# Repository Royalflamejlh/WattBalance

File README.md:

# ECE445-Wattbalance

## Introduction
Our senior design project focused on the development of a Kibble balance, also known as a watt balance. This is an instrument capable of precise measurements based on electromagnetic forces and the definition of a kilogram based on fundamental constants. Our design is focused on the two main working modes of a watt balance, velocity mode in which a coil constant is calculated, and force mode in which that coil constant is used to realize some mass. We designed a custom 3D printed balance, along with a custom PCB to drive the measurements. Once assembled we found that velocity mode on our balance was inaccurate, but our force mode performed as expected. With a manual estimation of the coil constant, we were able to get accurate mass readings from our balance. The designs, failures, and successes are all documented in the following report.

## Features
- **Custom 3D Printed Balance**: Designed for precise measurements.
- **Custom PCB**: For accurate measurement and control.
- **Velocity Mode**: Calculates the coil constant.
- **Force Mode**: Uses the coil constant to measure mass accurately.
- **Manual Estimation**: Allows for accurate mass readings.

## Read More
For more detailed information view:
- [Proposal](Documentation/proposal2.pdf)
- [Design Document](Documentation/design_document1.pdf)
- [Final Presentation](Documentation/other1.pdf)
- [Final Report](Documentation/final.pdf)

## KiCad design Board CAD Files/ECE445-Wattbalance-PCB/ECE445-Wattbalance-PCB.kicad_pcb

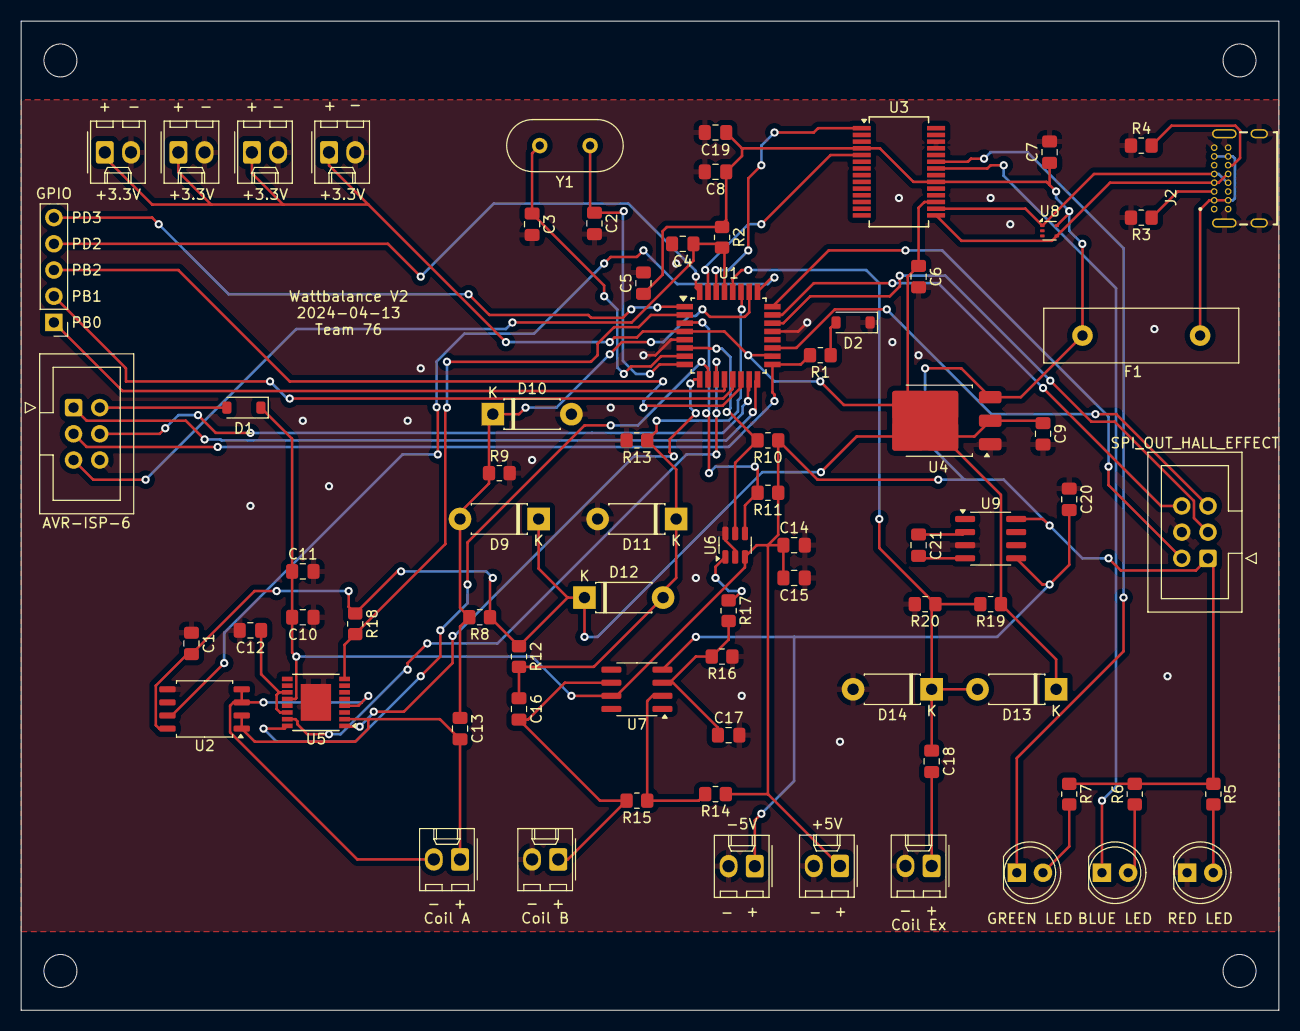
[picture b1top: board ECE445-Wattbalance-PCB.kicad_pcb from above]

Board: 2 copper layers, 121.9 x 95.9 mm, 80 parts (0 on the bottom side), 53 nets.

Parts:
C1: 0.1 µF; C_0805_2012Metric_Pad1.18x1.45mm_HandSolder
C2, C3: 22p; C_0805_2012Metric_Pad1.18x1.45mm_HandSolder
C4, C5: 100n; C_0805_2012Metric_Pad1.18x1.45mm_HandSolder
C6, C7, C8, C13, C16, C18: .1uF; C_0805_2012Metric_Pad1.18x1.45mm_HandSolder
C9, C11, C14, C19, C20, C21: 10uF; C_0805_2012Metric_Pad1.18x1.45mm_HandSolder
C10, C15: .1uf; C_0805_2012Metric_Pad1.18x1.45mm_HandSolder
C12: 2.2uF; C_0805_2012Metric_Pad1.18x1.45mm_HandSolder
C17: 0.1uF; C_0805_2012Metric_Pad1.18x1.45mm_HandSolder
D1: MBR0520; D_SOD-123
D2: D; D_SOD-123
D3: GREEN LED; LED_D5.0mm
D4: BLUE LED; LED_D5.0mm
D5: RED LED; LED_D5.0mm
D9, D10, D11, D12, D13, D14: 1N5819; D_DO-41_SOD81_P7.62mm_Horizontal
F1: 1A; Fuse_Littelfuse-LVR100
H1, H2, H3, H4: MountingHole; MountingHole_3.2mm_M3
J1: AVR-ISP-6; IDC-Header_2x03_P2.54mm_Vertical
J2: USB4085-GF-A_REVB; GCT_USB4085-GF-A_REVB
J3: SPI_OUT_HALL_EFFECT; IDC-Header_2x03_P2.54mm_Vertical
J4: GPIO; PinHeader_1x05_P2.54mm_Vertical
J5: Coil A; Molex_KK-254_AE-6410-02A_1x02_P2.54mm_Vertical
J6: Coil B; Molex_KK-254_AE-6410-02A_1x02_P2.54mm_Vertical
J7: Coil Ex; Molex_KK-254_AE-6410-02A_1x02_P2.54mm_Vertical
J8: -5V; Molex_KK-254_AE-6410-02A_1x02_P2.54mm_Vertical
J9, J11, J12, J13: +3.3V; Molex_KK-254_AE-6410-02A_1x02_P2.54mm_Vertical
J10: +5V; Molex_KK-254_AE-6410-02A_1x02_P2.54mm_Vertical
R1: 330R; R_0805_2012Metric_Pad1.20x1.40mm_HandSolder
R2, R8, R9, R10, R11, R12, R13, R18, R19, R20: 10k; R_0805_2012Metric_Pad1.20x1.40mm_HandSolder
R3, R4: 5.1k; R_0805_2012Metric_Pad1.20x1.40mm_HandSolder
R5, R6, R7: 470R; R_0805_2012Metric_Pad1.20x1.40mm_HandSolder
R14: 16k; R_0805_2012Metric_Pad1.20x1.40mm_HandSolder
R15, R16: 4k; R_0805_2012Metric_Pad1.20x1.40mm_HandSolder
R17: 6k; R_0805_2012Metric_Pad1.20x1.40mm_HandSolder
U1: ATmega328PB-A; TQFP-32_7x7mm_P0.8mm
U2: ACS70331EOLCTR-2P5B3; SOIC-8_5.23x5.23mm_P1.27mm
U3: FT232RL; SSOP-28_5.3x10.2mm_P0.65mm
U4: LM1117DT-3.3; TO-252-3_TabPin2
U5: DRV8848; TSSOP-16-1EP_4.4x5mm_P0.65mm
U6: MCP4725A2T-E/CH; SOT-23-6
U7: OPA188AIDBVR; SOIC-8_3.9x4.9mm_P1.27mm
U8: TPD3E001DRLR; SOT-553
U9: ICL7660; SOIC-8_3.9x4.9mm_P1.27mm
Y1: 16MHz; Crystal_HC49-U_Vertical

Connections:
+3.3V: C1.2, C6.1, C9.1, D9.1 (K), D12.1 (K), D13.1 (K), J9.1, J11.1, J12.1, J13.1, R8.1, R12.1, R18.1, R19.1, U1.4 (VCC), U1.18 (AVCC), U2.8 (VCC), U3.17 (3V3OUT), U4.2 (VO)
+5V: C5.1, C7.1, C8.1, C10.2, C11.1, C14.1, C15.2, C19.1, D1.1 (K), F1.2, J3.1, J10.1, R2.1, R5.1, R6.2, R7.1, R10.1, R11.1, R14.1, U3.4 (VCCIO), U3.20 (VCC), U4.3 (VI), U5.12 (VM), U6.3 (VDD), U7.7 (V+), U8.5, U9.8 (V+)
-5V: C20.2, J8.1, U7.4 (V-), U9.5 (VOUT)
/ACS70331_Vout: U1.25 (PC2), U2.7 (VIOUT)
/CoilA+: C13.2, J5.1, U2.1 (IP+), U2.2 (IP+), U5.2 (AOUT1)
/CoilA-: J5.2, U2.3 (IP-), U2.4 (IP-), U5.4 (AOUT2)
/CoilA_ADC: C13.1, D9.2 (A), D10.1 (K), R8.2, R9.1, U1.26 (PC3)
/CoilB+: C16.2, J6.1, R15.2, U7.6
/CoilB_ADC: C16.1, D11.1 (K), D12.2 (A), R12.2, R13.1, U1.27 (PC4)
/EXT+: C18.2, J7.1
/EXT_ADC: C18.1, D13.2 (A), D14.1 (K), R19.2, R20.1, U1.28 (PC5)
/HE_MISO: J3.6, U1.23 (PC0)
/HE_SCK: J3.2, U1.24 (PC1)
/H_FAULT: R18.2, U1.2 (PD4), U5.8 (~FAULT)
/H_SLEEP: U1.9 (PD5), U5.1 (~SLEEP)
/MISO: J1.1 (MISO), U1.16 (PB4)
/MOSI: J1.4 (MOSI), U1.15 (PB3)
/OUTA: J4.1, U1.12 (PB0)
/OUTB: J4.2, U1.13 (PB1)
/OUTC: J4.3, U1.14 (PB2)
/OUTD: J4.4, U1.32 (PD2)
/OUTE: J4.5, U1.1 (PD3)
/PWMA: U1.10 (PD6), U5.16 (AIN1)
/PWMB: U1.11 (PD7), U5.15 (AIN2)
/RST: C4.1, J1.5 (~RST), R2.2, U1.29 (~RESET/PC6)
/RX: U1.31 (PD1), U3.5 (RXD)
/RXLED: D4.1 (K), U3.22 (CBUS1)
/SCK: J1.3 (SCK), R1.2, U1.17 (PB5)
/SCL: R10.2, U1.6 (PE1), U6.5 (SCL)
/SDA: R11.2, U1.3 (PE0), U6.4 (SDA)
/TX: U1.30 (PD0), U3.1 (TXD)
/TXLED: D3.1 (K), U3.23 (CBUS0)
GND: C1.1, C2.2, C3.2, C4.2, C5.2, C6.2, C7.2, C8.2, C9.2, C10.1, C11.2, C12.2, C14.2, C15.1, C17.2, C19.2, C20.1, D2.1 (K), D5.1 (K), D10.2 (A), D11.2 (A), D14.2 (A), J1.6 (GND), J2.A1 (GND), J2.A12 (GND__1), J2.B1 (GND__2), J2.B12 (GND__3), J2.S1 (SHELL), J2.S2 (SHELL__1), J2.S3 (SHELL__2), J2.S4 (SHELL__3), J3.4, J6.2, J7.2, J8.2, J9.2, J10.2, J11.2, J12.2, J13.2, R3.2, R4.1, R9.2, R13.2, R16.1, R20.2, U1.5 (GND), U1.21 (GND), U2.5 (GND), U3.7 (GND), U3.18 (GND), U3.21 (GND), U3.25 (AGND), U3.26 (TEST), U4.1 (GND), U5.3 (AISEN), U5.13 (GND), U5.17 (GND), U6.2 (VSS), U6.6 (A0), U8.3, U9.3 (GND)
unnamed: D1.2 (A), J1.2 (VCC)
unnamed: D2.2 (A), R1.1
unnamed: D3.2 (A), R7.2
unnamed: D4.2 (A), R6.1
unnamed: D5.2 (A), R5.2
unnamed: J2.A5 (CC1), R3.1
unnamed: J2.B5 (CC2), R4.2
unnamed: J2.A7 (DN1), J2.B7 (DN2), U3.16 (USBD-), U8.1 (IO1)
unnamed: J2.A6 (DP1), J2.B6 (DP2), U3.15 (USBD+), U8.4 (IO3)
unnamed: F1.1, J2.A4 (VBUS), J2.A9 (VBUS__1), J2.B4 (VBUS__2), J2.B9 (VBUS__3)
unnamed: J3.3, U1.22 (PE3)
unnamed: J3.5, U1.19 (PE2)
unnamed: C3.1, U1.7 (XTAL1/PB6), Y1.2
unnamed: C2.1, U1.8 (XTAL2/PB7), Y1.1
unnamed: C12.1, U5.11 (VREF), U5.14 (VINT)
unnamed: R17.1, U6.1 (VOUT)
unnamed: C17.1, R16.2, R17.2, U7.3 (+)
unnamed: R14.2, R15.1, U7.2 (-)
unnamed: C21.1, U9.2 (CAP+)
unnamed: C21.2, U9.4 (CAP-)

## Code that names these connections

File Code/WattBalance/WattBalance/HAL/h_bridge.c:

#include "h_bridge.h"
#include <avr/io.h>
#include <math.h>
#include "../config.h"
#include "../timer.h"

/*-----------------------------------------------------------------
 * PWM Half Bridge Control (DRV8848)
 * Ports PD4 (H_FAULT), PD5 (H_SLEEP), PD6 (PWMA), PD7 (PWMB)
 *-----------------------------------------------------------------*/

static volatile u8 duty_cycle = 0;
static volatile u8 current_tick = 0;

void pwm_callback(){
	if (current_tick < duty_cycle) {
		PORTD |= (1 << PORTD6) | (1 << PORTD7);  // Set PD6 and PD7 high.
	} else {
		PORTD &= ~((1 << PORTD6) | (1 << PORTD7));  // Set PD6 and PD7 low.
	}
	current_tick = (current_tick + 1) % DUTY_CYCLE_LENGTH;
}

void set_pwm(u16 new_duty_cycle) {
	duty_cycle = (new_duty_cycle * DUTY_CYCLE_LENGTH) / 100; // Turn percentage into a tick
}

void init_hb(void){
	current_tick = 0; // Reset current tick value.
	
	DDRD |= (1 << PORTD6) | (1 << PORTD7); // Setup D6 and D7 for Output.
	
	DDRD  |= (1 << PORTD4);  // Enable D4 for output.
	PORTD &= ~(1 << PORTD4); // Make D4 active low.
	
	DDRD &= ~(1 << PORTD5);  // Enable PD5 as an input.
	PORTD |= (1 << PORTD5);  // Enable pull-up resistor on PD5.
	
	PORTD |= (1 << PORTD4);  // Enable chip setting sleep high.
	
}

void start_pwm(){
	current_tick = 0; // Reset current tick value.
	init_timer2(HB_TIMER, pwm_callback); // Start the timer
}

void stop_pwm(){
	stop_timer2(); // Stop the timer to stop the output
	current_tick = 0; // Reset current tick value.
	PORTD &= ~((1 << PORTD6) | (1 << PORTD7));  // Set PD6 and PD7 low.
}

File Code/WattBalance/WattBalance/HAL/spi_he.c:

/*-----------------------------------------------------------------
 * Hall Effect Sensor (ERCK 05SPI 360) SPI Setup
 * Ports PE3 (MOSI), PE2 (SS), PC0 (MISO), PC1 (SCK)
 *-----------------------------------------------------------------*/
void init_spi_he(void){
	
}

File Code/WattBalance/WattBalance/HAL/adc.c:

#include "adc.h"
#include <avr/io.h>
#include "../config.h"
/*-----------------------------------------------------------------
 * ADC Voltage Readings
 * Ports PC3 (Coil A), PC4 (Coil B), PC5 (Extra), PC2 (Current Sensor)
 *-----------------------------------------------------------------*/

/*
* init_adc
* This function enables ADC capabilities on the ATMega
*/
void init_adc(void) {
	ADMUX = ADC_REF_AVCC;
	ADCSRA = ADC_ENABLE | ADC_PRESCALER_128;
}

/* read_adc
 * Reads an ADC value from a specified channel.
 * Parameters: channel - ADC channel to read
 * Returns: ADC conversion result as a uint16_t
 */
u16 read_adc(u8 channel){
	ADMUX = (ADMUX & 0xF0) | (channel & 0x0F);
	ADCSRA |= (1<<ADSC);
	while (ADCSRA & (1<<ADSC));
	return ADC;
}

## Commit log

2024-07-31 Created github repo of Watt Balance project
2024-07-31 Moved Final pdf
2024-07-31 Added picture
